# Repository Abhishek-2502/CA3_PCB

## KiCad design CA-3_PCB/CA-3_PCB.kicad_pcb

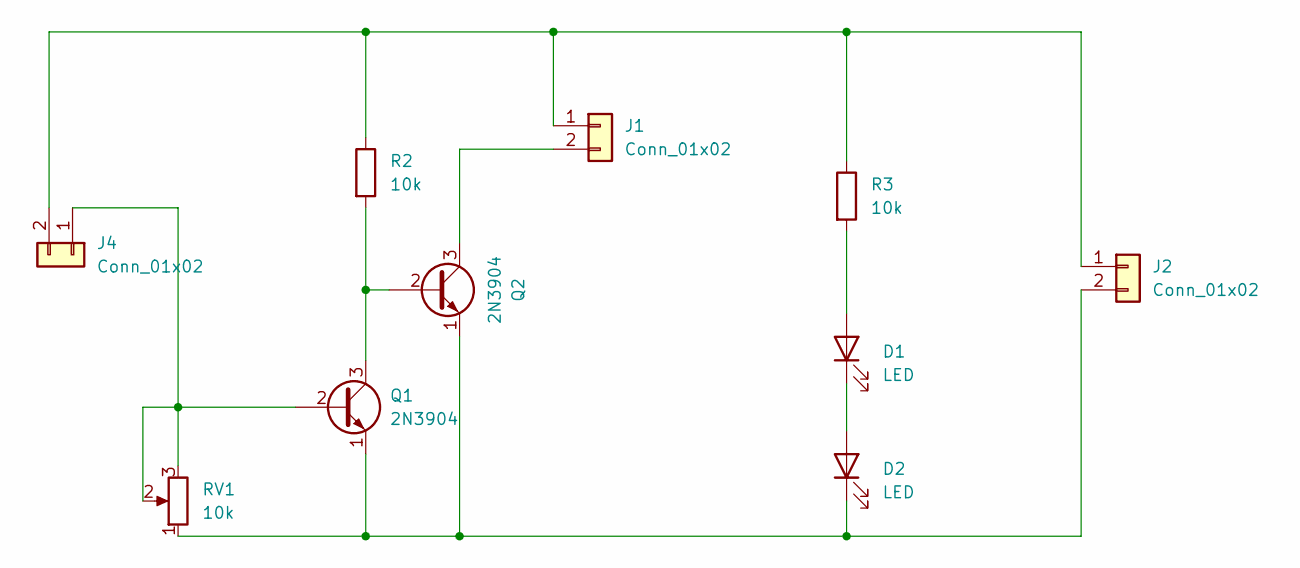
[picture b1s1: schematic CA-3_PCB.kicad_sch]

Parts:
D1, D2: LED; LED_D3.0mm
J1, J2, J4: Conn_01x02; AMASS_XT30UPB-M_1x02_P5.0mm_Vertical
Q1, Q2: 2N3904; TO-92_Inline
R2, R3: 10k; R_Axial_DIN0207_L6.3mm_D2.5mm_P10.16mm_Horizontal
RV1: 10k; Potentiometer_Vishay_148-149_Single_Horizontal

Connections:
unnamed: D1.2 (A), R3.2
unnamed: D1.1 (K), D2.2 (A)
unnamed: D2.1 (K), J2.2, Q1.1 (E), Q2.1 (E), RV1.1
unnamed: J1.1, J2.1, J4.2, R2.1, R3.1
unnamed: J1.2, Q2.3 (C)
unnamed: J4.1, Q1.2 (B), RV1.2, RV1.3
unnamed: Q1.3 (C), Q2.2 (B), R2.2

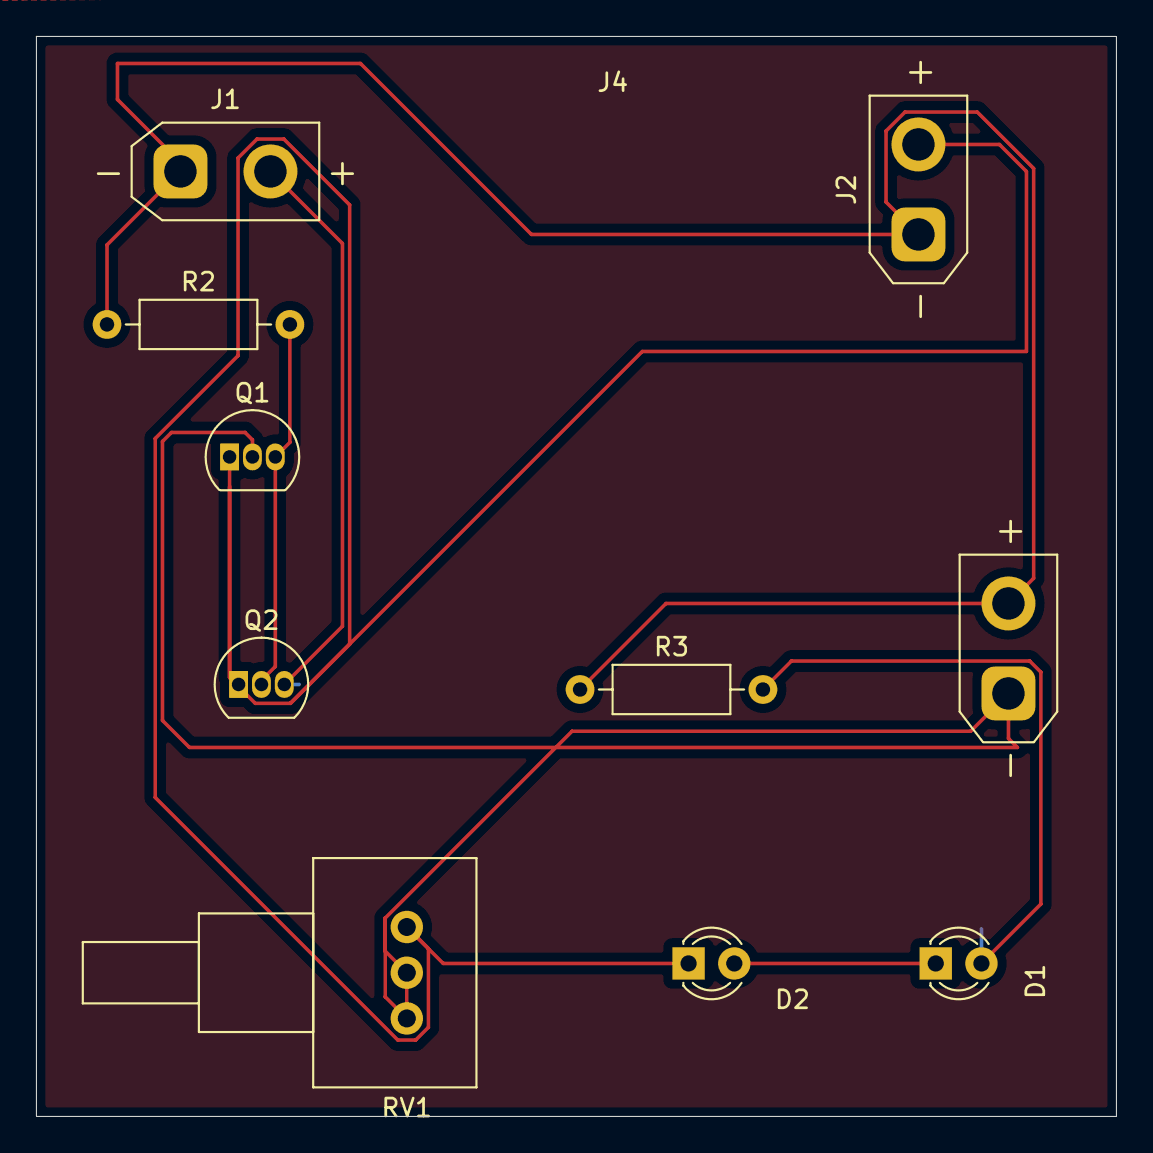
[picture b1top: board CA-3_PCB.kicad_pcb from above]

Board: 2 copper layers, 60.0 x 60.0 mm, 10 parts (0 on the bottom side), 7 nets.

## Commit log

2025-04-07 Added Project
2025-04-27 Added Report
